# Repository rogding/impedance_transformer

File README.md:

# impedance_transformer

Based on information from https://www.kkn.net/~n6tv/XFMR/

PCB design for Red Pitaya impedance transformer to convert 50 ohm signal to Red Pitaya's high impedance inputs.

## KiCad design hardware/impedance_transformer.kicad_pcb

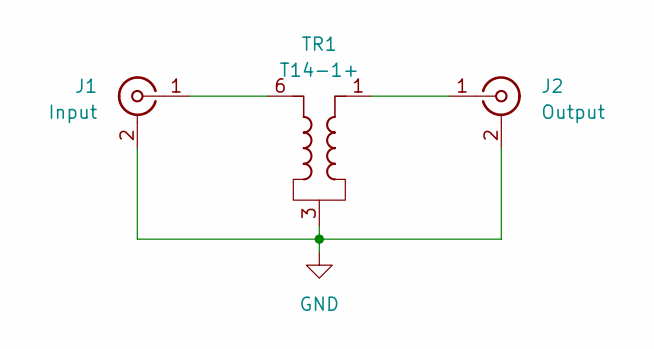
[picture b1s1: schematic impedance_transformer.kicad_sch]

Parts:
J1: Input; SMA_Amphenol_901-143_Horizontal
J2: Output; SMA_Amphenol_901-143_Horizontal
TR1: T14-1+; Mini-Circuits_W38

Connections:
GND: J1.2 (Ext), J2.2 (Ext), TR1.3
unnamed: J1.1 (In), TR1.6
unnamed: J2.1 (In), TR1.1

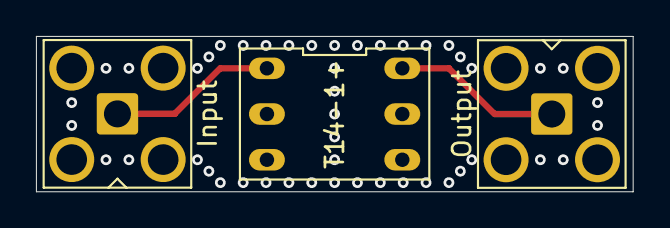
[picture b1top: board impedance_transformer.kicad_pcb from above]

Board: 4 copper layers, 33.2 x 8.6 mm, 3 parts (0 on the bottom side), 3 nets.

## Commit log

2025-03-30 Added N6TV documentation
2025-03-30 Started KiCad project
2025-03-31 First draft of PCB
